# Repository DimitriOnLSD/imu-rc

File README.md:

# IMU-RC
This repository contains the final project for an Electronics and Computer Engineering degree: IMU-RC, an innovative hand-held controller for RC cars.

## Features
### Hand Unit
The hand unit is a battery-powered controller featuring:

- ESP32-S3 WROOM module on a custom PCB designed in KiCad.
- LSM6DSO IMU sensor for motion detection.
- BLE communication using a client/server protocol with the RC car.
- OLED screen (128x32) for menu options, diagnostics, and sensitivity adjustments.
- Four buttons for navigation: Back, Up, Select, Down.
- RGB LED to display battery or communication status.
- Battery Management System (BMS) with BQ297 and MCP73831 to charge a 3.7V 250mAh LiPo battery via USB-C.
- BOOT and RESET buttons for easy firmware handling.

### Gesture-Based Control
Control the RC car with intuitive hand gestures:

- Lean forward: Car moves forward.
- Lean backward: Car reverses.
- Lean left or right: Car rotates left or right.
- Control mode toggle: For 4-motor vehicles with omni-directional wheels, enable sideways movement for strafing.

### Additional Features
- Car stats menu: Check car battery levels.
- Safety mechanism: Infrared proximity sensors prevent collision with walls/objects:
  - 2-motor cars: Front and back sensors.
  - 4-motor cars: Side sensors added for additional safety during strafing.
  
### Technical Highlights
- Custom PCB: Designed in KiCad for compact, efficient performance.
- Battery Management: MCP73831 handles charging, and BQ297 ensures protection against overcharging/discharging.
- Versatile Control: Adaptable to different RC car configurations (2-motor or 4-motor).
- OLED Menu System: Offers detailed settings, diagnostics, and real-time feedback.

### Usage
IMU-RC is designed to bring modern, intuitive control to RC vehicles, making it a perfect blend of technology and engineering creativity.

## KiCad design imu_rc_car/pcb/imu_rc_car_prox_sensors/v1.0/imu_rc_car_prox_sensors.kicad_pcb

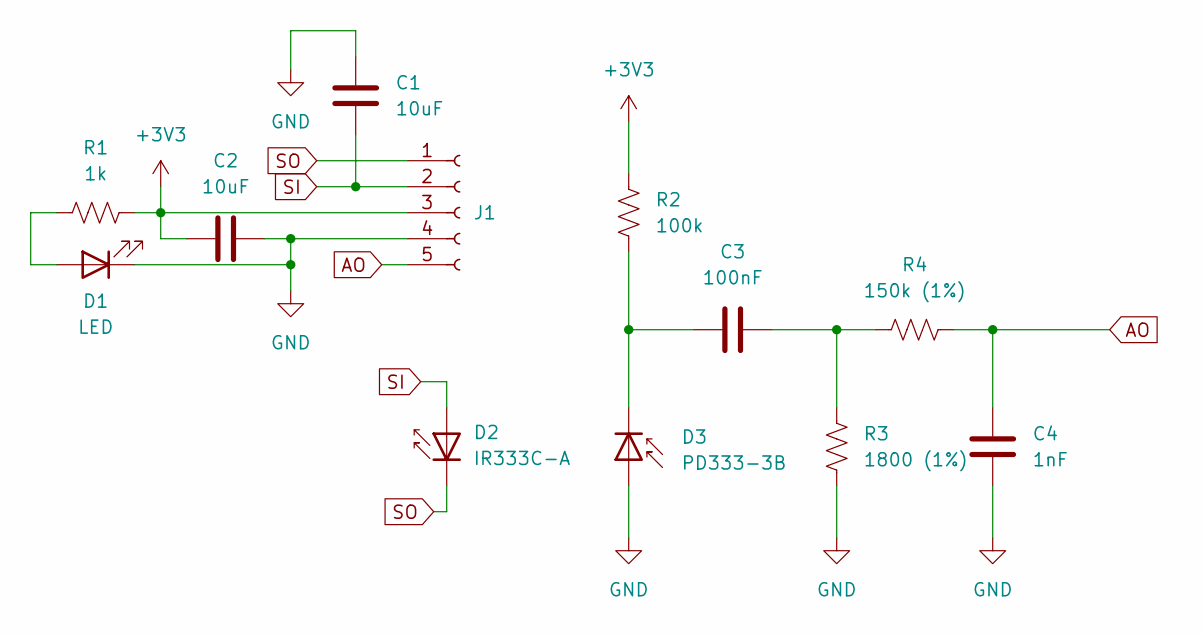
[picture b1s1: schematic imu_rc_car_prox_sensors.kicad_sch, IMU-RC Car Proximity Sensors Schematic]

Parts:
C1, C2: 10uF; C_0805_2012Metric
C3: 100nF; C_0805_2012Metric
C4: 1nF; C_0805_2012Metric
D1: LED; LED_0805_2012Metric
D2: IR333C-A; LED_D5.0mm_Horizontal_O1.27mm_Z3.0mm_Clear
D3: PD333-3B; LED_D5.0mm_Horizontal_O1.27mm_Z3.0mm_IRBlack
J1: Conn_01x05_Socket; JST_PH_S5B-PH-SM4-TB_1x05-1MP_P2.00mm_Horizontal
R1: 1k; R_0805_2012Metric
R2: 100k; R_0805_2012Metric
R3: 1800 (1%); R_0805_2012Metric
R4: 150k (1%); R_0805_2012Metric

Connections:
+3V3: C2.2, J1.3, R1.2, R2.2
AO: C4.2, J1.5, R4.1
GND: C1.1, C2.1, C4.1, D1.1 (K), D3.2 (A), J1.4, R3.1
unnamed: C3.2, R3.2, R4.2
unnamed: D1.2 (A), R1.1
unnamed: C3.1, D3.1 (K), R2.1
SI: C1.2, D2.2 (A), J1.2
SO: D2.1 (K), J1.1

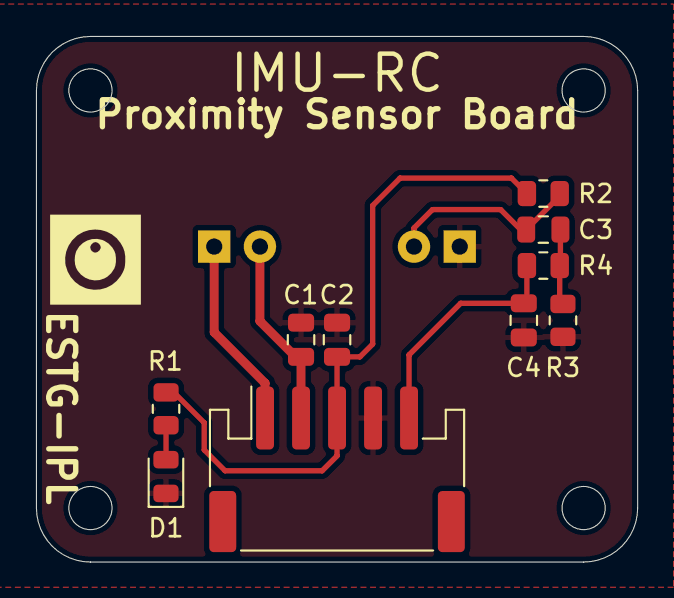
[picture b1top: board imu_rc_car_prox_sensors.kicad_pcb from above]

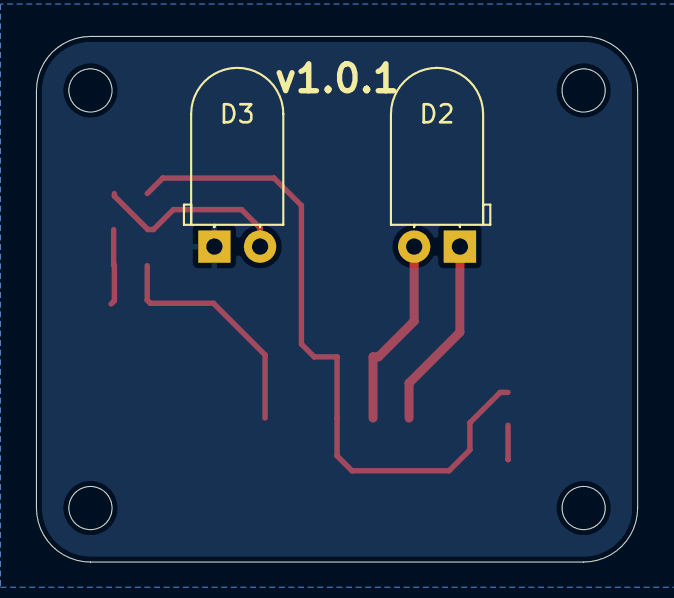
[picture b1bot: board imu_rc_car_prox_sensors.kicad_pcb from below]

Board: 2 copper layers, 33.4 x 29.2 mm, 12 parts (2 on the bottom side), 8 nets.

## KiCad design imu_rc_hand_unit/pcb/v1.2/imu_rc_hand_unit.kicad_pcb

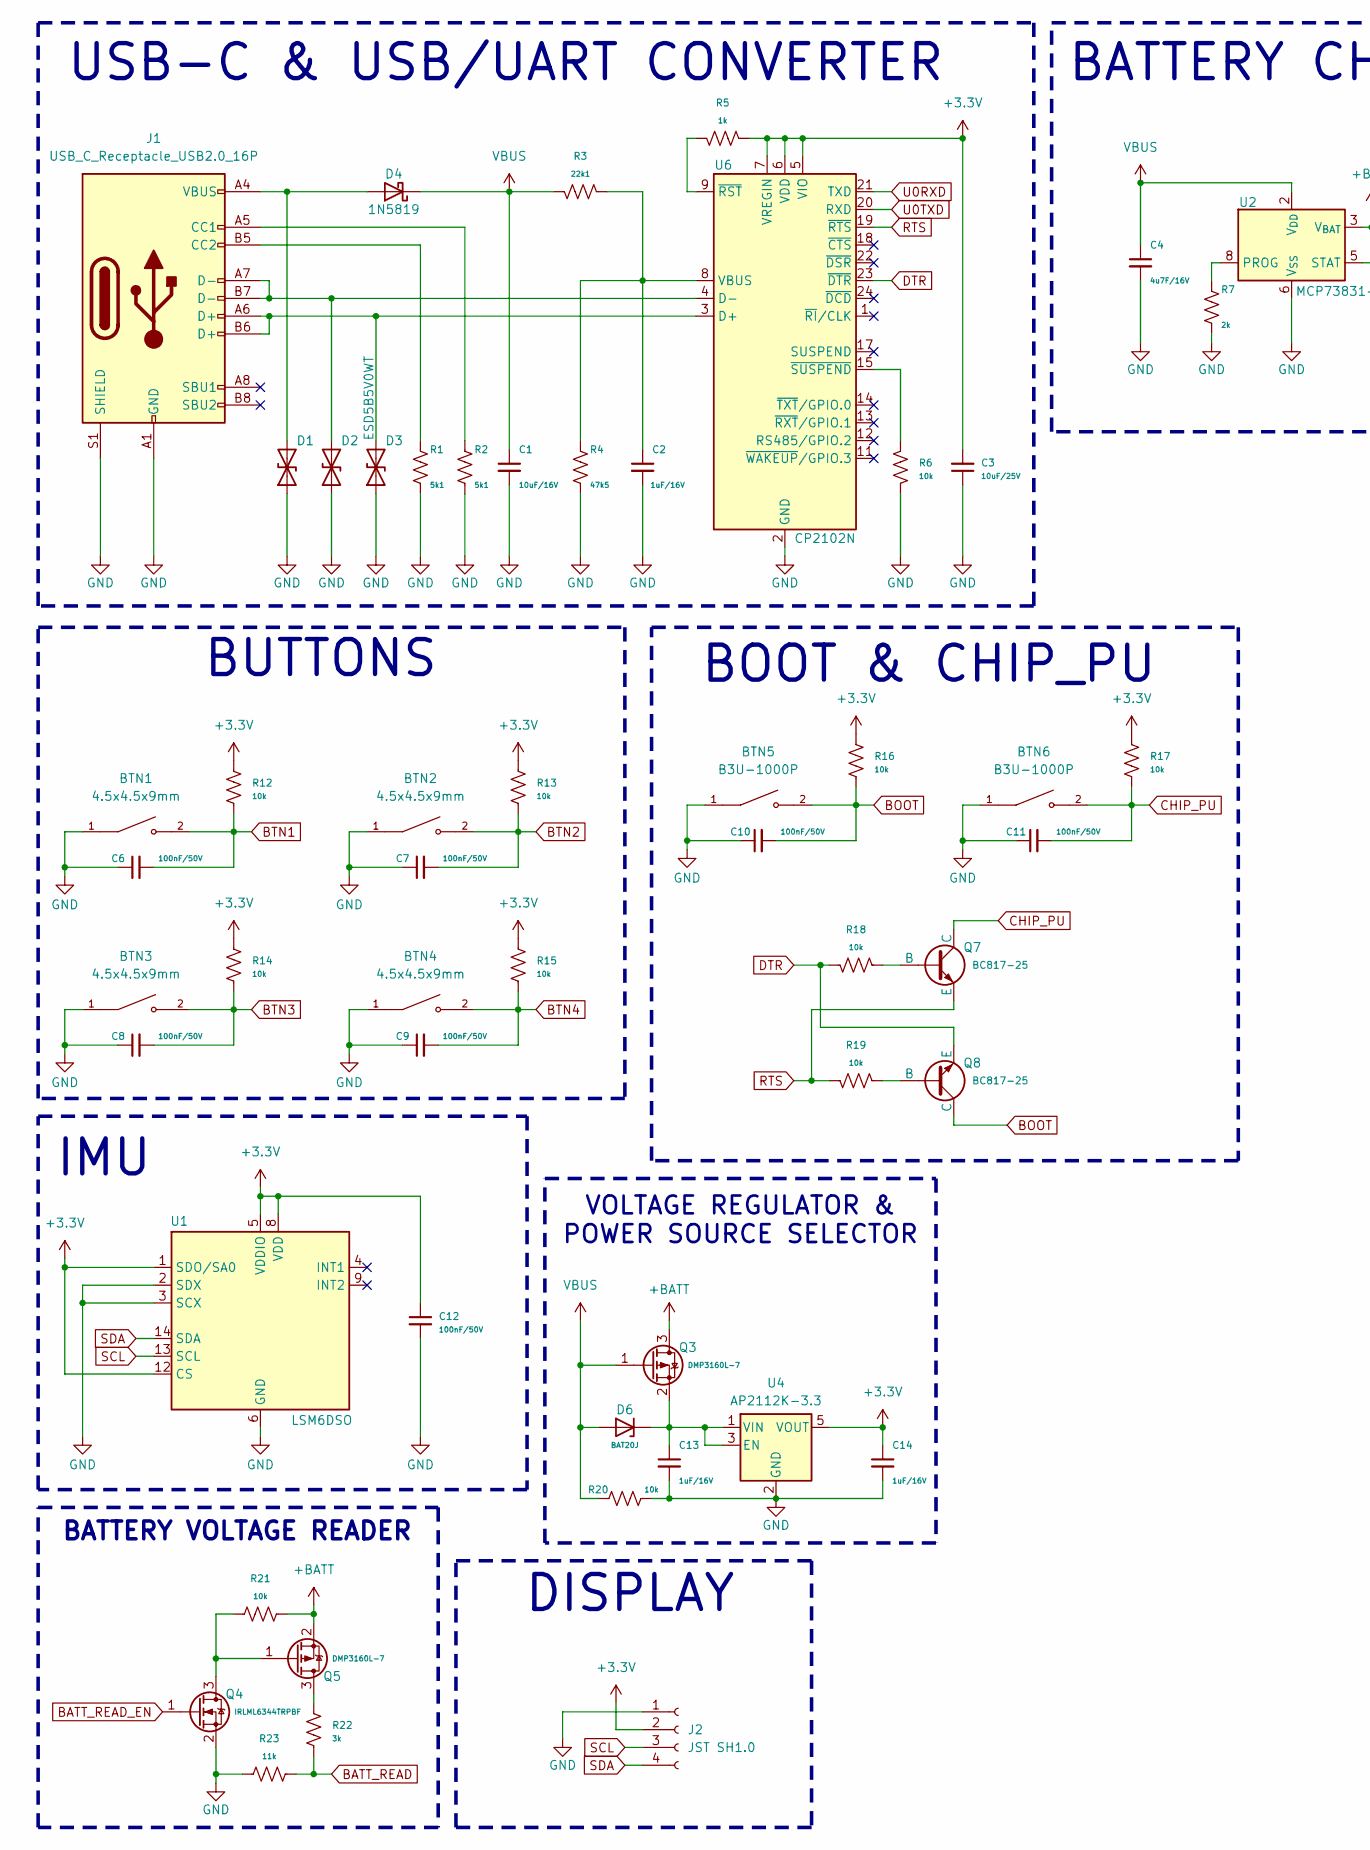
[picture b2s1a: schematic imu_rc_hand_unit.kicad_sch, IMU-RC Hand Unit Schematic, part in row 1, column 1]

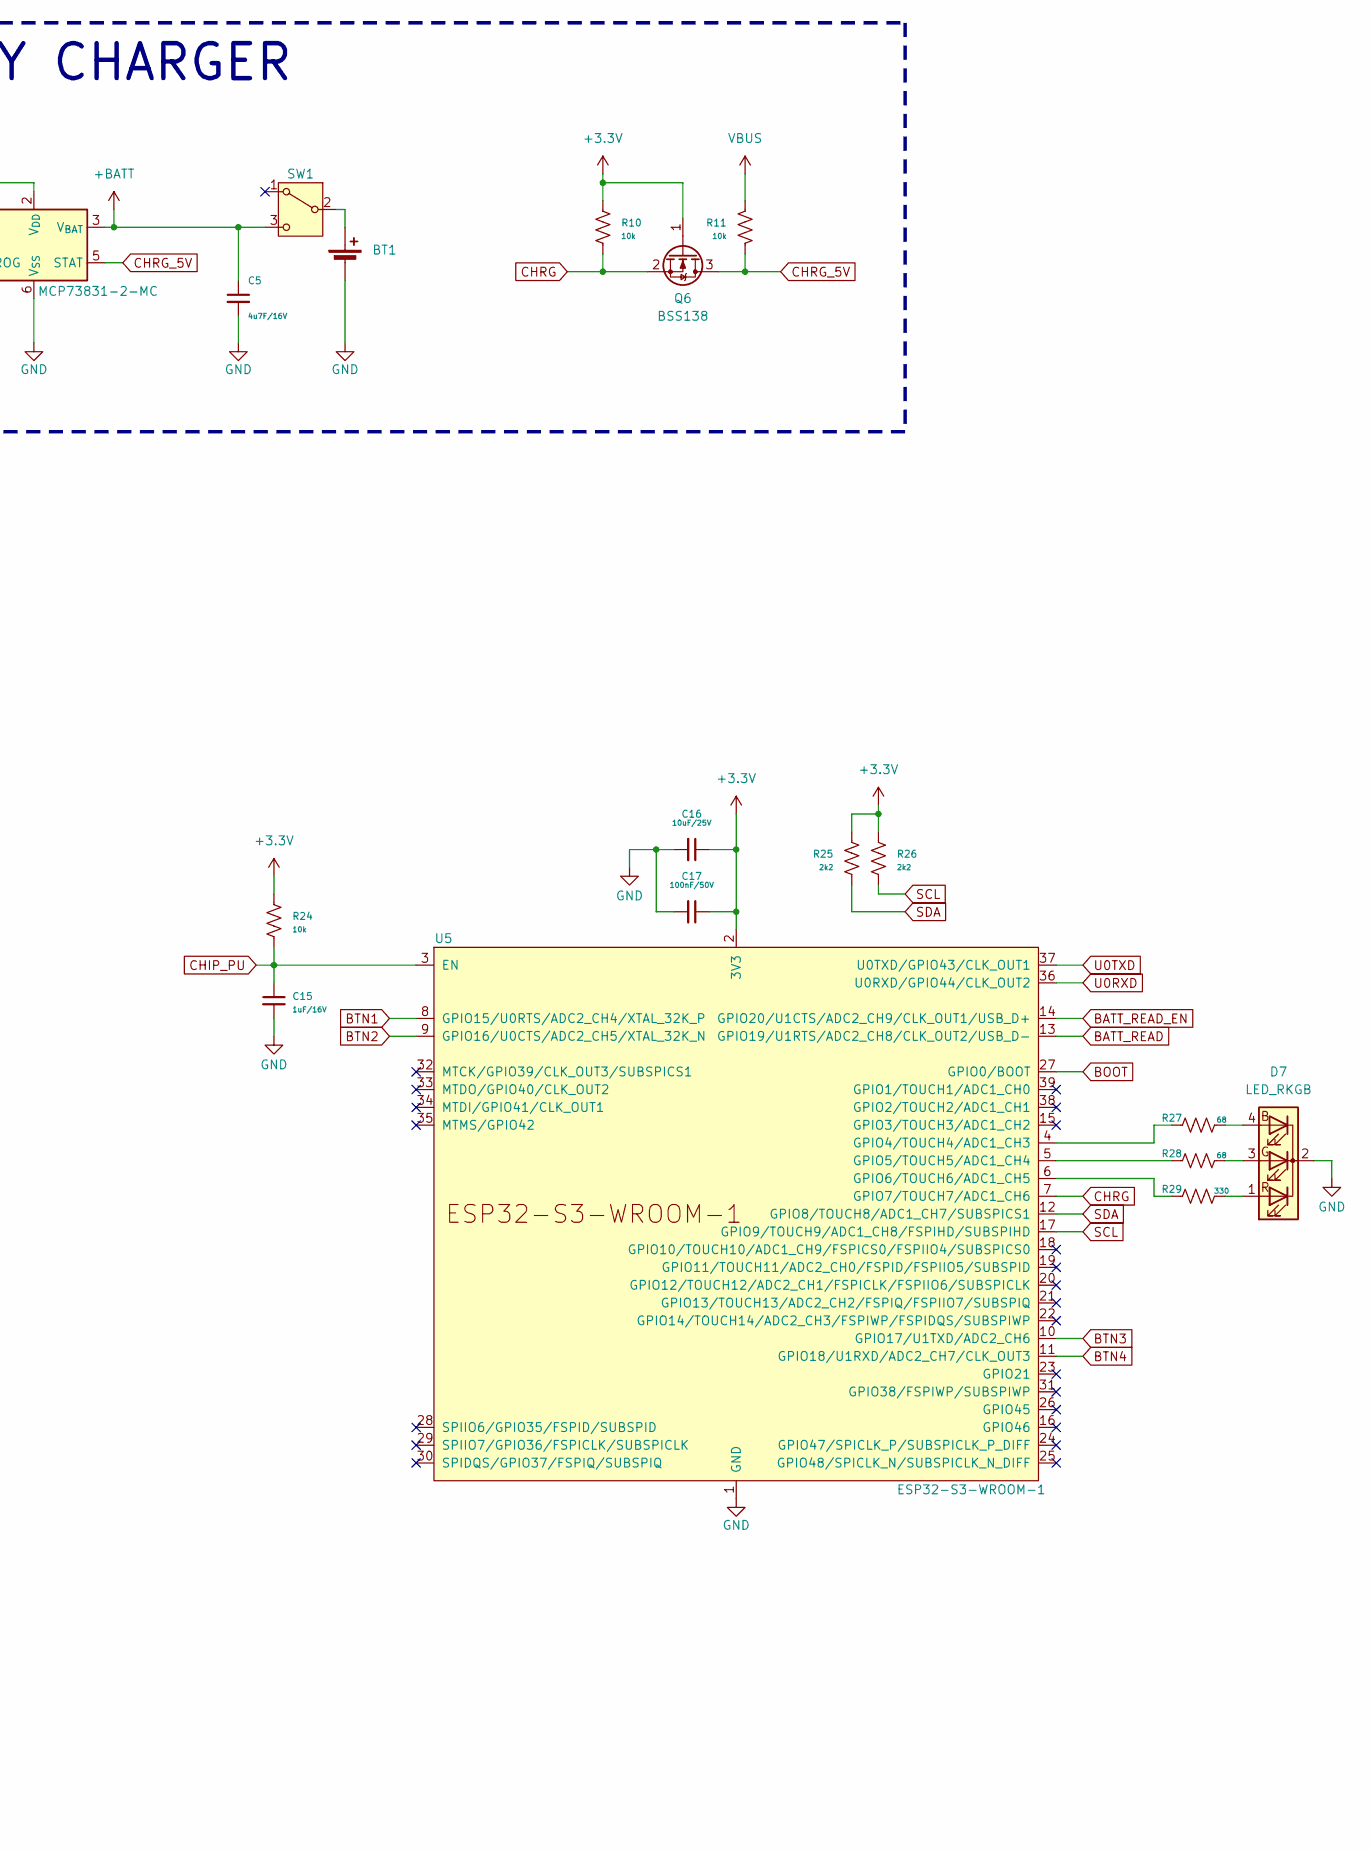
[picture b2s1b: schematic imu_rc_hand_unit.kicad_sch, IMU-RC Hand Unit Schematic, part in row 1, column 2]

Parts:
BT1: LiPo 3.7V 600mAh; JST_PH_S2B-PH-K_1x02_P2.00mm_Horizontal
BTN1, BTN2, BTN3, BTN4: 4.5x4.5x9mm; SW_SPST_PTS647_Sx50
BTN5, BTN6: B3U-1000P; SW_SPST_B3U-1000P
C1: 10uF/16V; C_0805_2012Metric
C2: 1uF/16V; C_0603_1608Metric
C3: 10uF/25V; C_0603_1608Metric
C4, C5: 4u7F/16V; C_0603_1608Metric
C6, C7, C8, C9, C10, C11, C12, C17: 100nF/50V; C_0805_2012Metric
C13, C14, C15: 1uF/16V; C_0805_2012Metric
C16: 10uF/25V; C_0805_2012Metric
D1, D2, D3: ESD5B5V0WT; D_SOD-523
D4: 1N5819; D_SOD-123
D6: BAT20J; D_SOD-323
D7: LED_RKGB; LED_D5.0mm-4_RKGB
J1: USB_C_Receptacle_USB2.0_16P; USB_C_Receptacle_GCT_USB4105-xx-A_16P_TopMnt_Horizontal
J2: JST SH1.0; JST_SH_SM04B-SRSS-TB_1x04-1MP_P1.00mm_Horizontal
Q3, Q5: DMP3160L-7; SOT-23
Q4: IRLML6344TRPBF; SOT-23
Q6: BSS138; SOT-23
Q7, Q8: BC817-25; SOT-23
R1, R2: 5k1; R_0805_2012Metric
R3: 22k1; R_0805_2012Metric
R4: 47k5; R_0805_2012Metric
R5: 1k; R_0805_2012Metric
R6, R10, R11, R12, R13, R14, R15, R16, R17, R18, R19, R20, R21, R24: 10k; R_0805_2012Metric
R7: 2k; R_0805_2012Metric
R22: 3k; R_0805_2012Metric
R23: 11k; R_0805_2012Metric
R25, R26: 2k2; R_0805_2012Metric
R27, R28: 68; R_0805_2012Metric
R29: 330; R_0805_2012Metric
SW1: SW_SPDT; SW_Slide_SPDT_Angled_CK_OS102011MA1Q
U1: LSM6DSO; LGA-14L_3x2.5mm_P0.5mm
U2: MCP73831-2-MC; DFN-8-1EP_3x2mm_P0.5mm_EP1.7x1.4mm
U4: AP2112K-3.3; SOT-23-5
U5: ESP32-S3-WROOM-1
U6: CP2102N; QFN-24-1EP_4x4mm_P0.5mm_EP2.6x2.6mm

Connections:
+3.3V: C3.2, C12.1, C14.1, C16.1, C17.1, J2.2, Q6.1 (G), R5.2, R10.2, R12.2, R13.2, R14.2, R15.2, R16.2, R17.2, R24.2, R25.1, R26.2, U1.1 (SDO/SA0), U1.5 (VDDIO), U1.8 (VDD), U1.12 (CS), U4.5 (VOUT), U5.2 (3V3), U6.5 (VIO), U6.6 (VDD), U6.7 (VREGIN)
BATT_READ: R22.2, R23.1, U5.13 (GPIO19/U1RTS/ADC2_CH8/CLK_OUT2/USB_D-)
BATT_READ_EN: Q4.1 (G), U5.14 (GPIO20/U1CTS/ADC2_CH9/CLK_OUT1/USB_D+)
BOOT: BTN5.2, C10.2, Q8.1 (C), R16.1, U5.27 (GPIO0/BOOT); also elsewhere on the board
BTN1: BTN1.2, C6.2, R12.1, U5.8 (GPIO15/U0RTS/ADC2_CH4/XTAL_32K_P)
BTN2: BTN2.2, C7.2, R13.1, U5.9 (GPIO16/U0CTS/ADC2_CH5/XTAL_32K_N)
BTN3: BTN3.2, C8.2, R14.1, U5.10 (GPIO17/U1TXD/ADC2_CH6)
BTN4: BTN4.2, C9.2, R15.1, U5.11 (GPIO18/U1RXD/ADC2_CH7/CLK_OUT3)
CHIP_PU: BTN6.2, C11.2, C15.1, Q7.1 (C), R17.1, R24.1, U5.3 (EN); also elsewhere on the board
CHRG: Q6.2 (S), R10.1, U5.7 (GPIO7/TOUCH7/ADC1_CH6)
CHRG_5V: Q6.3 (D), R11.1, U2.5 (STAT)
DTR: Q8.3 (E), R18.1, U6.23 (~DTR)
unnamed: BT1.1 (+), SW1.2 (B)
unnamed: D1.2 (A2), D4.2 (A), J1.A4 (VBUS), J1.A9 (VBUS), J1.B4 (VBUS), J1.B9 (VBUS)
unnamed: D2.2 (A2), J1.A7 (D-), J1.B7 (D-), U6.4 (D-)
unnamed: D3.2 (A2), J1.A6 (D+), J1.B6 (D+), U6.3 (D+)
unnamed: C13.1, D6.1 (K), Q3.2 (S), U4.1 (VIN), U4.3 (EN)
unnamed: D7.4 (BA), R27.1
unnamed: D7.3 (GA), R28.1
unnamed: D7.1 (RA), R29.1
unnamed: J1.A5 (CC1), R2.2
unnamed: J1.B5 (CC2), R1.2
unnamed: Q4.3 (D), Q5.1 (G), R21.1
unnamed: Q5.3 (D), R22.1
unnamed: Q7.2 (B), R18.2
unnamed: Q8.2 (B), R19.2
unnamed: R7.1, U2.8 (PROG)
unnamed: R27.2, U5.4 (GPIO4/TOUCH4/ADC1_CH3)
unnamed: R28.2, U5.5 (GPIO5/TOUCH5/ADC1_CH4)
unnamed: R29.2, U5.6 (GPIO6/TOUCH6/ADC1_CH5)
unnamed: C2.1, R3.1, R4.2, U6.8 (VBUS)
unnamed: R5.1, U6.9 (~RST)
unnamed: R6.1, U6.15 (~SUSPEND)
RTS: Q7.3 (E), R19.1, U6.19 (~RTS)
SCL: J2.3, R26.1, U1.13 (SCL), U5.17 (GPIO9/TOUCH9/ADC1_CH8/FSPIHD/SUBSPIHD)
SDA: J2.4, R25.2, U1.14 (SDA), U5.12 (GPIO8/TOUCH8/ADC1_CH7/SUBSPICS1)
U0RXD: U5.36 (U0RXD/GPIO44/CLK_OUT2), U6.21 (TXD)
U0TXD: U5.37 (U0TXD/GPIO43/CLK_OUT1), U6.20 (RXD)
VBUS: C1.1, C4.1, D4.1 (K), D6.2 (A), Q3.1 (G), R3.2, R11.2, R20.2, U2.1 (V_{DD}), U2.2 (V_{DD})

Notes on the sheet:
VOLTAGE REGULATOR & POWER SOURCE SELECTOR
BATTERY CHARGER
BUTTONS
BOOT & CHIP_PU
USB-C & USB/UART CONVERTER
BATTERY VOLTAGE READER
IMU
DISPLAY

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
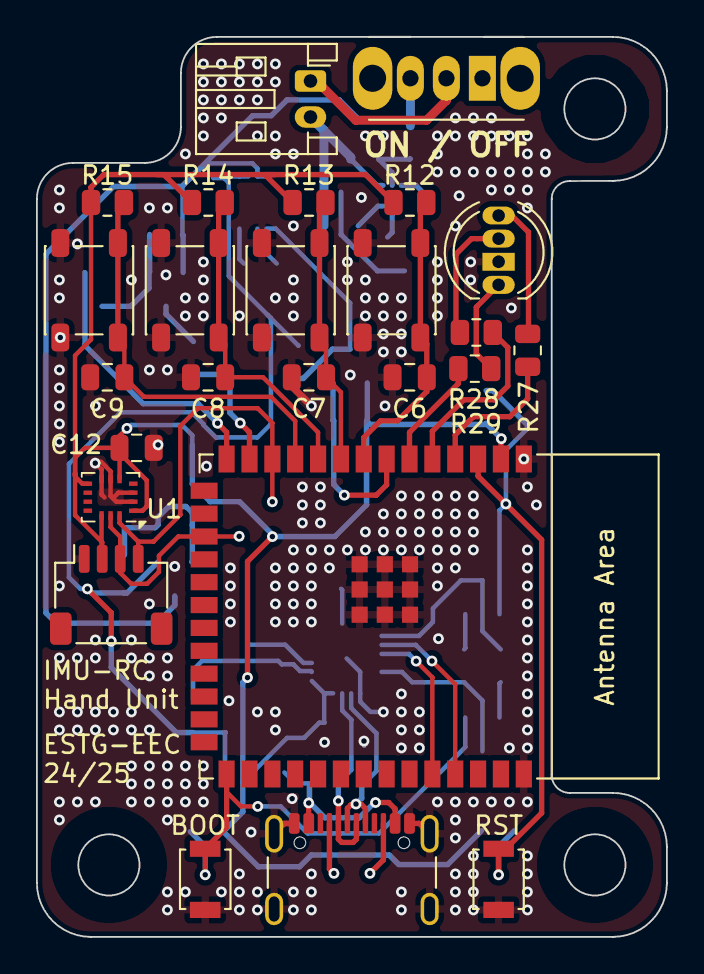
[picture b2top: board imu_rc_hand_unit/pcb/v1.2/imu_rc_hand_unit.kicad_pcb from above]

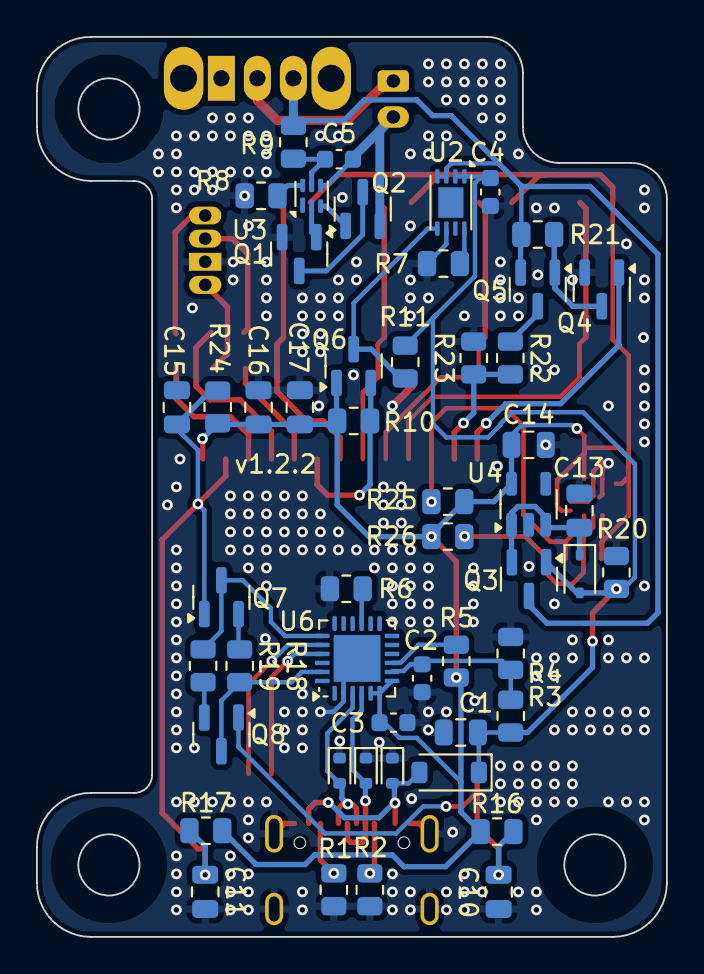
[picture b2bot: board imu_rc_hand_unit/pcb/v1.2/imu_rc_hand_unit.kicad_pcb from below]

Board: 2 copper layers, 35.0 x 50.0 mm, 76 parts (51 on the bottom side), 47 nets.

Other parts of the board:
BOOT: B3U-1000P; SW_SPST_B3U-1000P
Q1, Q2: IRLML6344TRPBF; SOT-23
R8: 2k2; R_0805_2012Metric
R9: 330; R_0805_2012Metric
RST: B3U-1000P; SW_SPST_B3U-1000P
U3: BQ297xy; WSON-6_1.5x1.5mm_P0.5mm

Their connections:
BOOT: BOOT.2; also elsewhere on the board
CHIP_PU: RST.2; also elsewhere on the board
unnamed: Q1.3 (D), Q2.3 (D)
unnamed: Q1.1 (G), U3.2 (Cout)
unnamed: Q2.1 (G), U3.3 (Dout)
unnamed: R8.2, U3.6 (V-)

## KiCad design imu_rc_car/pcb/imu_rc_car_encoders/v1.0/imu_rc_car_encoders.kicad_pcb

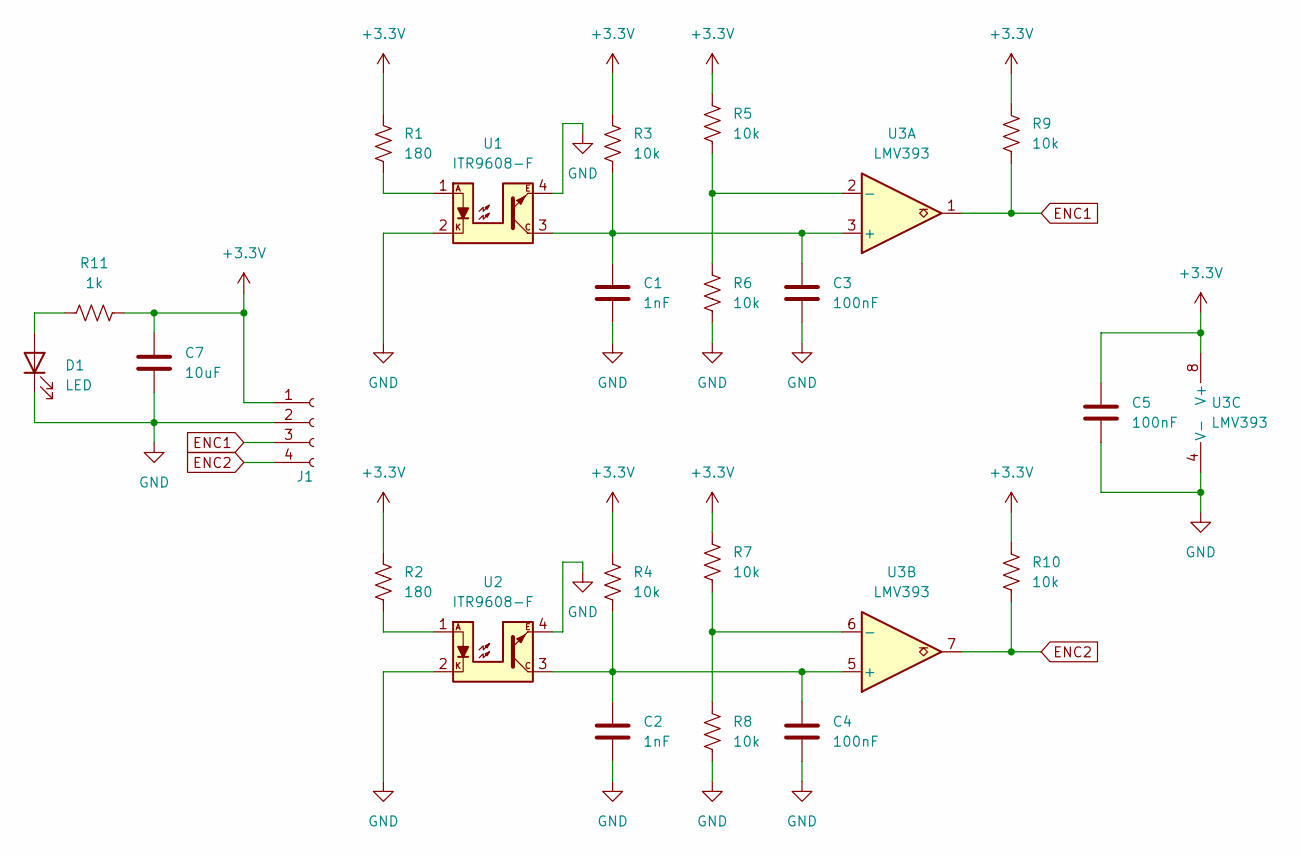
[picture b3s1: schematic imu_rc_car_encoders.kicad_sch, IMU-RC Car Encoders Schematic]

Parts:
C1, C2: 1nF; C_0805_2012Metric
C3, C4, C5: 100nF; C_0805_2012Metric
C7: 10uF; C_0805_2012Metric
D1: LED; LED_0805_2012Metric
J1: Conn_01x04_Socket; JST_PH_S4B-PH-SM4-TB_1x04-1MP_P2.00mm_Horizontal
R1, R2: 180; R_0805_2012Metric
R3, R4, R5, R6, R7, R8, R9, R10: 10k; R_0805_2012Metric
R11: 1k; R_0805_2012Metric
U1, U2: ITR9608-F; Everlight_ITR9608-F
U3: LMV393; SOIC-8_3.9x4.9mm_P1.27mm

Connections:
+3.3V: C5.1, C7.1, J1.1, R1.1, R2.1, R3.1, R4.1, R5.1, R7.1, R9.1, R10.1, R11.2, U3.8 (V+)
ENC1: J1.3, R9.2, U3.1
ENC2: J1.4, R10.2, U3.7
GND: C1.2, C2.2, C3.2, C4.2, C5.2, C7.2, D1.1 (K), J1.2, R6.2, R8.2, U1.2, U1.4, U2.2, U2.4, U3.4 (V-)
unnamed: D1.2 (A), R11.1
unnamed: R1.2, U1.1
unnamed: R2.2, U2.1
unnamed: C1.1, C3.1, R3.2, U1.3, U3.3 (+)
unnamed: R5.2, R6.1, U3.2 (-)
unnamed: C2.1, C4.1, R4.2, U2.3, U3.5 (+)
unnamed: R7.2, R8.1, U3.6 (-)

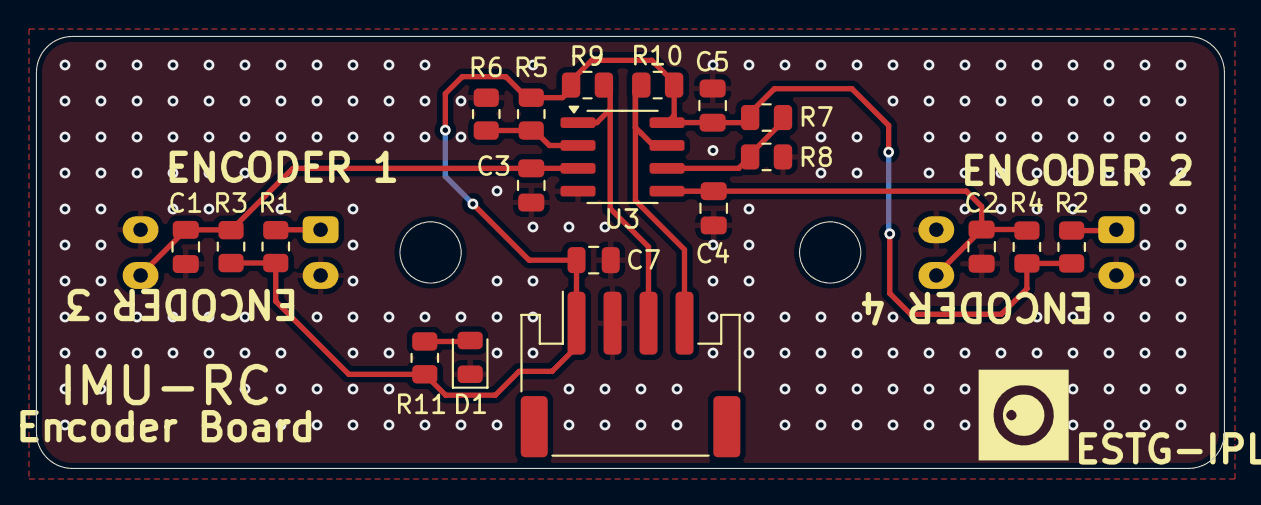
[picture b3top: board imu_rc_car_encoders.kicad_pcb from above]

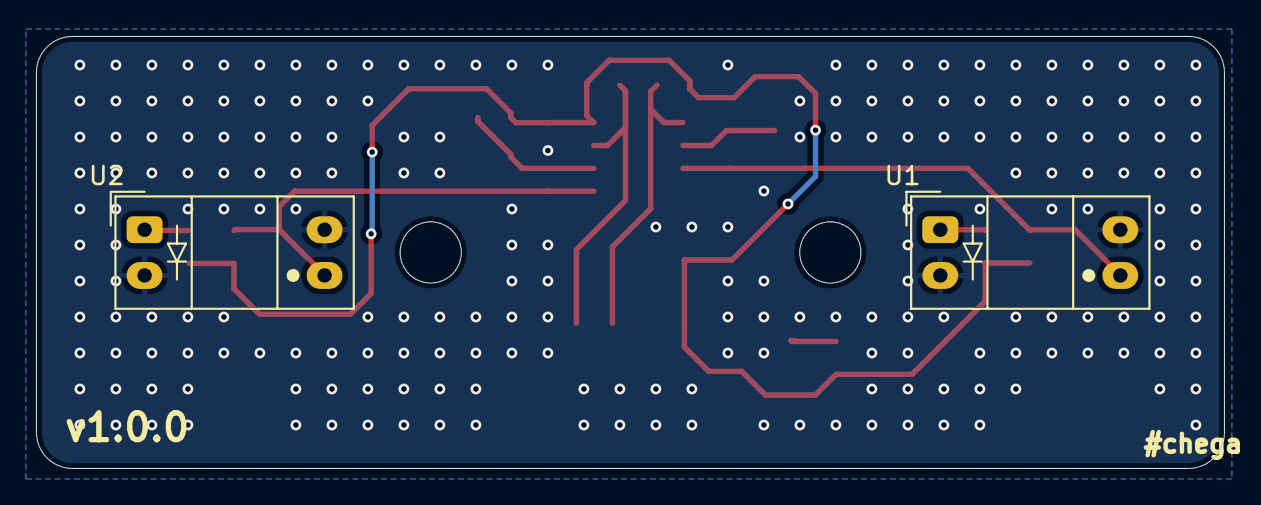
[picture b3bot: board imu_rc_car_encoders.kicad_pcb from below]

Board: 2 copper layers, 66.0 x 24.0 mm, 22 parts (2 on the bottom side), 11 nets.

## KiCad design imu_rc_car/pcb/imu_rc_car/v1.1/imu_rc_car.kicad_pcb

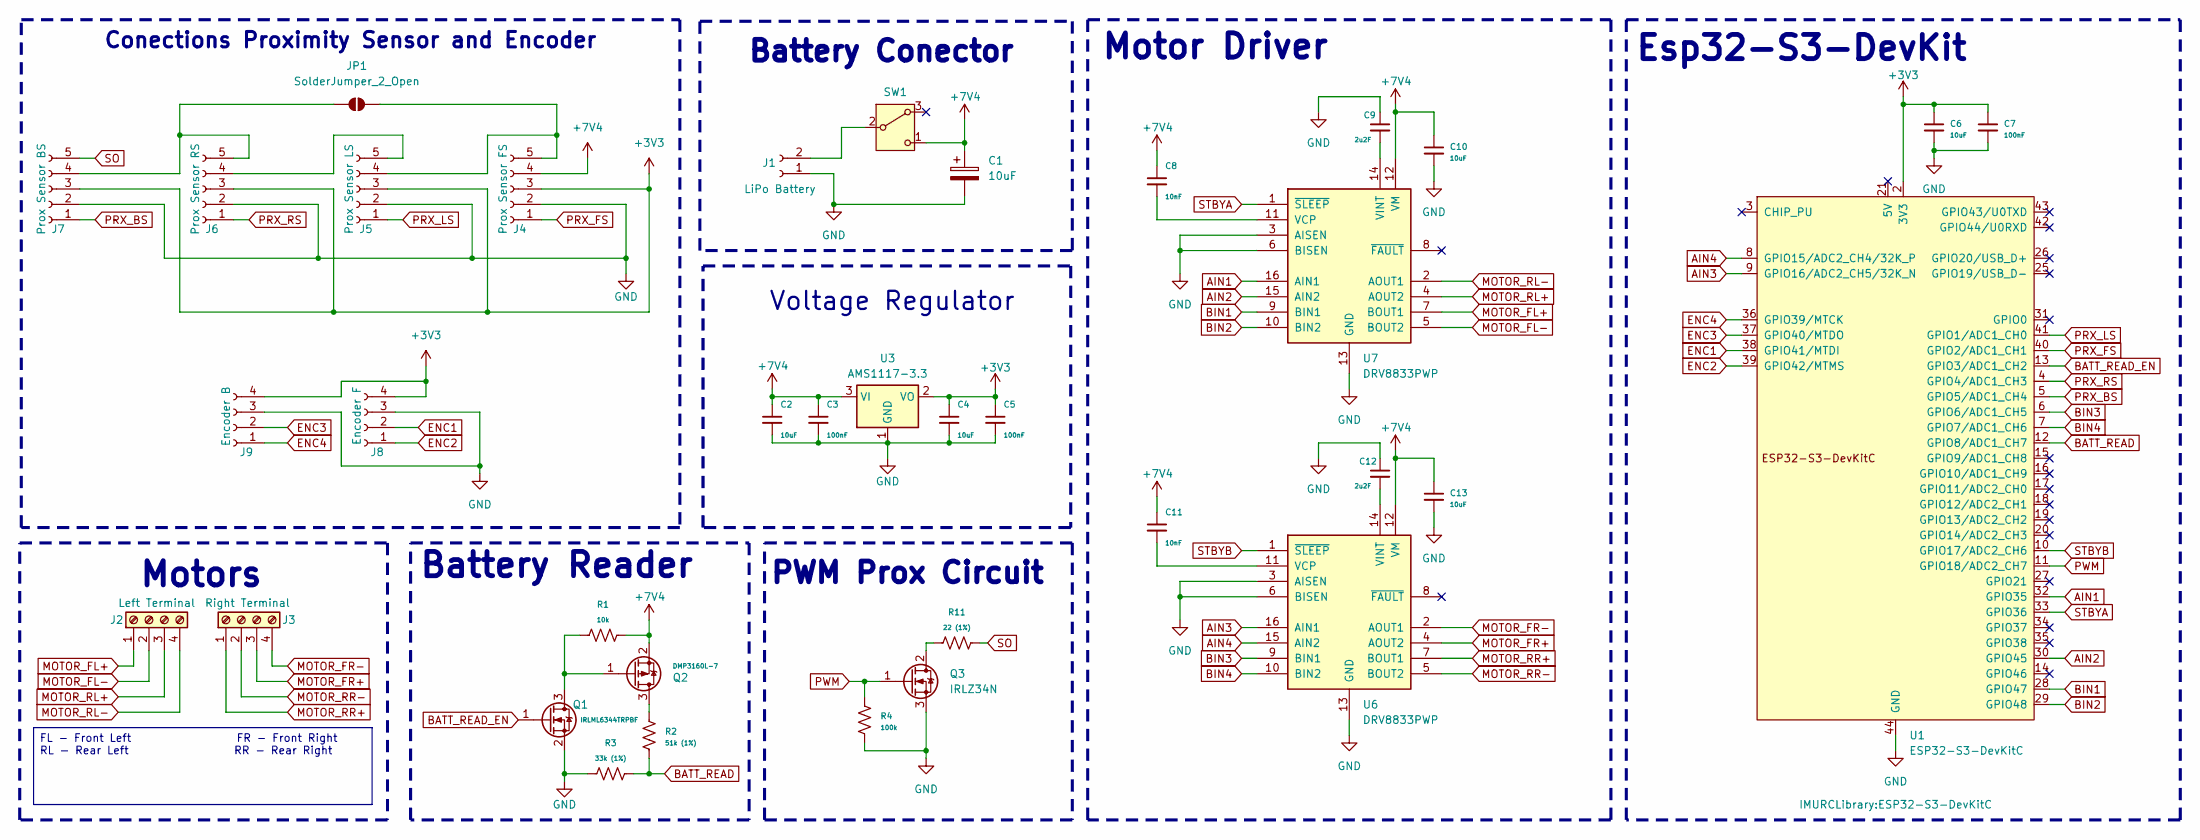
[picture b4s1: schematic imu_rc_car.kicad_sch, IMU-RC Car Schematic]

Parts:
C1: 10uF; CP_Elec_5x5.7
C2, C4, C6, C10, C13: 10uF; C_0805_2012Metric
C3, C5, C7: 100nF; C_0805_2012Metric
C8, C11: 10nF; C_0805_2012Metric
C9, C12: 2u2F; C_0805_2012Metric
J1: LiPo Battery; TerminalBlock_MaiXu_MX126-5.0-02P_1x02_P5.00mm
J2: Left Terminal; TerminalBlock_Xinya_XY308-2.54-4P_1x04_P2.54mm_Horizontal
J3: Right Terminal; TerminalBlock_Xinya_XY308-2.54-4P_1x04_P2.54mm_Horizontal
J4: Prox Sensor FS; JST_PH_S5B-PH-SM4-TB_1x05-1MP_P2.00mm_Horizontal
J5: Prox Sensor LS; JST_PH_S5B-PH-SM4-TB_1x05-1MP_P2.00mm_Horizontal
J6: Prox Sensor RS; JST_PH_S5B-PH-SM4-TB_1x05-1MP_P2.00mm_Horizontal
J7: Prox Sensor BS; JST_PH_S5B-PH-SM4-TB_1x05-1MP_P2.00mm_Horizontal
J8: Encoder F; JST_PH_S4B-PH-SM4-TB_1x04-1MP_P2.00mm_Horizontal
J9: Encoder B; JST_PH_S4B-PH-SM4-TB_1x04-1MP_P2.00mm_Horizontal
JP1: SolderJumper_2_Open; SolderJumper-2_P1.3mm_Open_RoundedPad1.0x1.5mm
Q1: IRLML6344TRPBF; SOT-23
Q2: DMP3160L-7; SOT-23
Q3: IRLZ34N; TO-263-3_TabPin2
R1: 10k; R_0805_2012Metric
R2: 51k (1%); R_0805_2012Metric
R3: 33k (1%); R_0805_2012Metric
R4: 100k; R_0805_2012Metric
R11: 22 (1%); R_0805_2012Metric
SW1: SW_Nidec_CAS-120A1; SW_Slide_SPDT_Angled_CK_OS102011MA1Q
U1: ESP32-S3-DevKitC
U3: AMS1117-3.3; SOT-223-3_TabPin2
U6, U7: DRV8833PWP; HTSSOP-16-1EP_4.4x5mm_P0.65mm_EP3.4x5mm_Mask2.46x2.31mm_The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

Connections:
+3V3: C4.1, C5.1, C6.1, C7.1, J4.3, J5.3, J6.3, J7.3, J8.4, J9.4, U1.1 (3V3), U1.2 (3V3), U3.2 (VO)
+7V4: C1.1, C2.1, C3.1, C8.1, C10.1, C11.1, C13.1, J4.4, Q2.2 (S), R1.2, SW1.1 (C), U3.3 (VI), U6.12 (VM), U7.12 (VM)
AIN1: U1.32 (GPIO35), U7.16 (AIN1)
AIN2: U1.30 (GPIO45), U7.15 (AIN2)
AIN3: U1.9 (GPIO16/ADC2_CH5/32K_N), U6.16 (AIN1)
AIN4: U1.8 (GPIO15/ADC2_CH4/32K_P), U6.15 (AIN2)
BATT_READ: R2.2, R3.1, U1.12 (GPIO8/ADC1_CH7)
BATT_READ_EN: Q1.1 (G), U1.13 (GPIO3/ADC1_CH2)
BIN1: U1.28 (GPIO47), U7.9 (BIN1)
BIN2: U1.29 (GPIO48), U7.10 (BIN2)
BIN3: U1.6 (GPIO6/ADC1_CH5), U6.9 (BIN1)
BIN4: U1.7 (GPIO7/ADC1_CH6), U6.10 (BIN2)
ENC1: J8.2, U1.38 (GPIO41/MTDI)
ENC2: J8.1, U1.39 (GPIO42/MTMS)
ENC3: J9.2, U1.37 (GPIO40/MTDO)
ENC4: J9.1, U1.36 (GPIO39/MTCK)
GND: C1.2, C2.2, C3.2, C4.2, C5.2, C6.2, C7.2, C9.1, C10.2, C12.1, C13.2, J1.1, J4.2, J5.2, J6.2, J7.2, J8.3, J9.3, Q1.2 (S), Q3.3 (S), R3.2, R4.2, U1.22 (GND), U1.23 (GND), U1.24 (GND), U1.44 (GND), U3.1 (GND), U6.3 (AISEN), U6.6 (BISEN), U6.13 (GND), U6.17 (GND), U7.3 (AISEN), U7.6 (BISEN), U7.13 (GND), U7.17 (GND)
MOTOR_FL+: J2.1, U7.7 (BOUT1)
MOTOR_FL-: J2.2, U7.5 (BOUT2)
MOTOR_FR+: J3.3, U6.4 (AOUT2)
MOTOR_FR-: J3.4, U6.2 (AOUT1)
MOTOR_RL+: J2.3, U7.4 (AOUT2)
MOTOR_RL-: J2.4, U7.2 (AOUT1)
MOTOR_RR+: J3.1, U6.7 (BOUT1)
MOTOR_RR-: J3.2, U6.5 (BOUT2)
unnamed: J1.2, SW1.2 (B)
unnamed: J4.5, J5.4, JP1.2 (B)
unnamed: J5.5, J6.4
unnamed: J6.5, J7.4, JP1.1 (A)
unnamed: Q1.3 (D), Q2.1 (G), R1.1
unnamed: Q2.3 (D), R2.1
unnamed: Q3.2 (D), R11.1
unnamed: C11.2, U6.11 (VCP)
unnamed: C12.2, U6.14 (VINT)
unnamed: C8.2, U7.11 (VCP)
unnamed: C9.2, U7.14 (VINT)
PRX_BS: J7.1, U1.5 (GPIO5/ADC1_CH4)
PRX_FS: J4.1, U1.40 (GPIO2/ADC1_CH1)
PRX_LS: J5.1, U1.41 (GPIO1/ADC1_CH0)
PRX_RS: J6.1, U1.4 (GPIO4/ADC1_CH3)
PWM: Q3.1 (G), R4.1, U1.11 (GPIO18/ADC2_CH7)
SO: J7.5, R11.2
STBYA: U1.33 (GPIO36), U7.1 (~SLEEP)
STBYB: U1.10 (GPIO17/ADC2_CH6), U6.1 (~SLEEP)

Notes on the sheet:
Voltage Regulator
Battery Conector
PWM Prox Circuit
Motor Driver
Conections Proximity Sensor and Encoder
Esp32-S3-DevKit
Motors
Battery Reader
FL - Front Left FR - Front Right RL - Rear Left RR - Rear Right

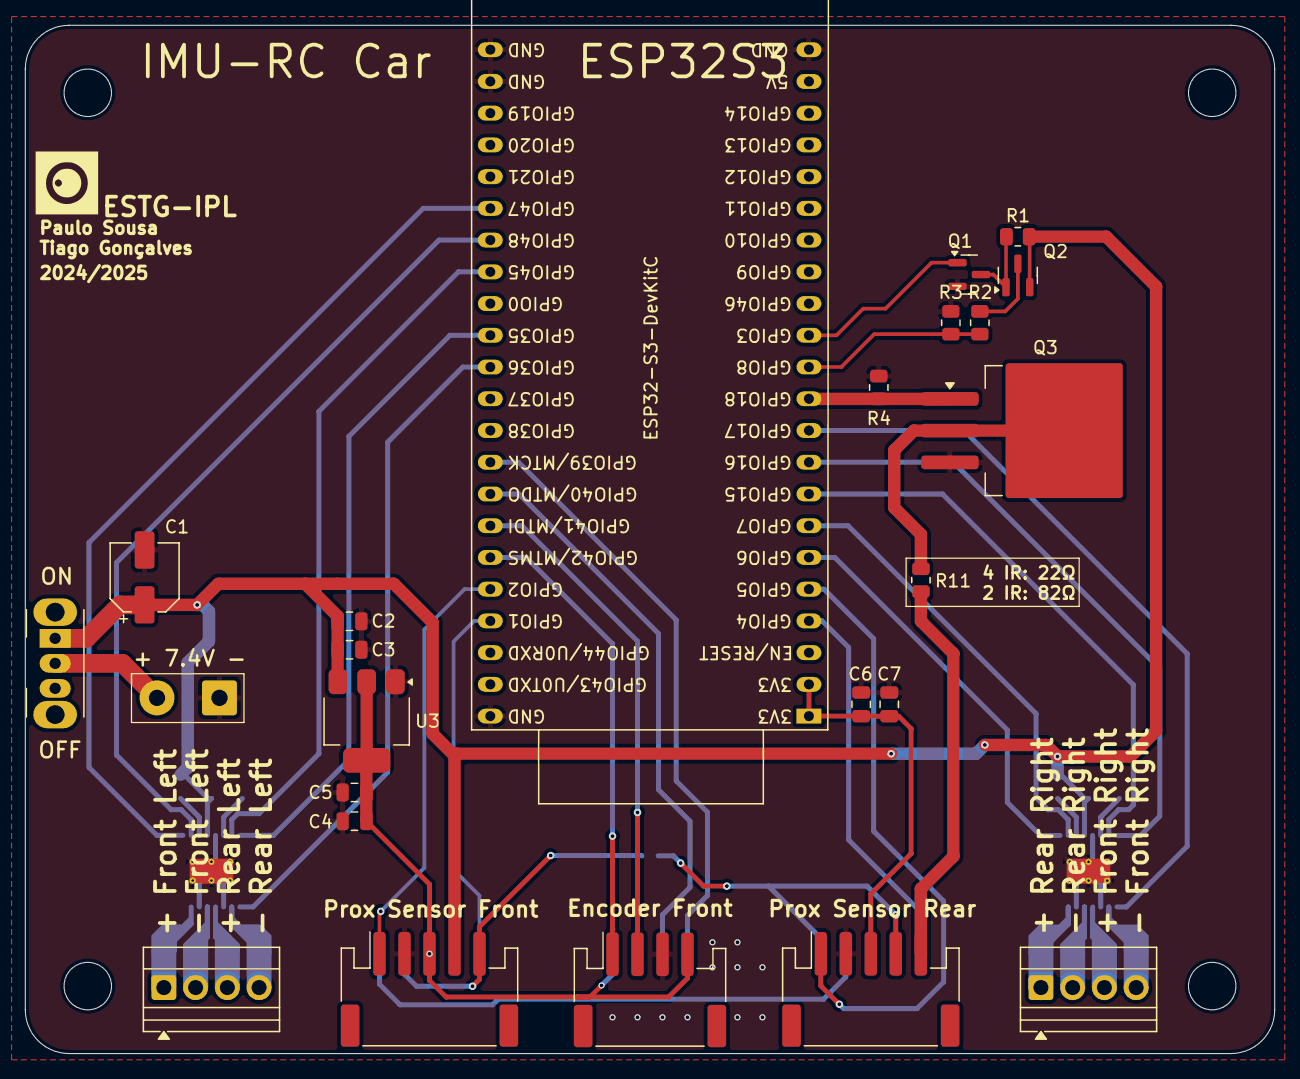
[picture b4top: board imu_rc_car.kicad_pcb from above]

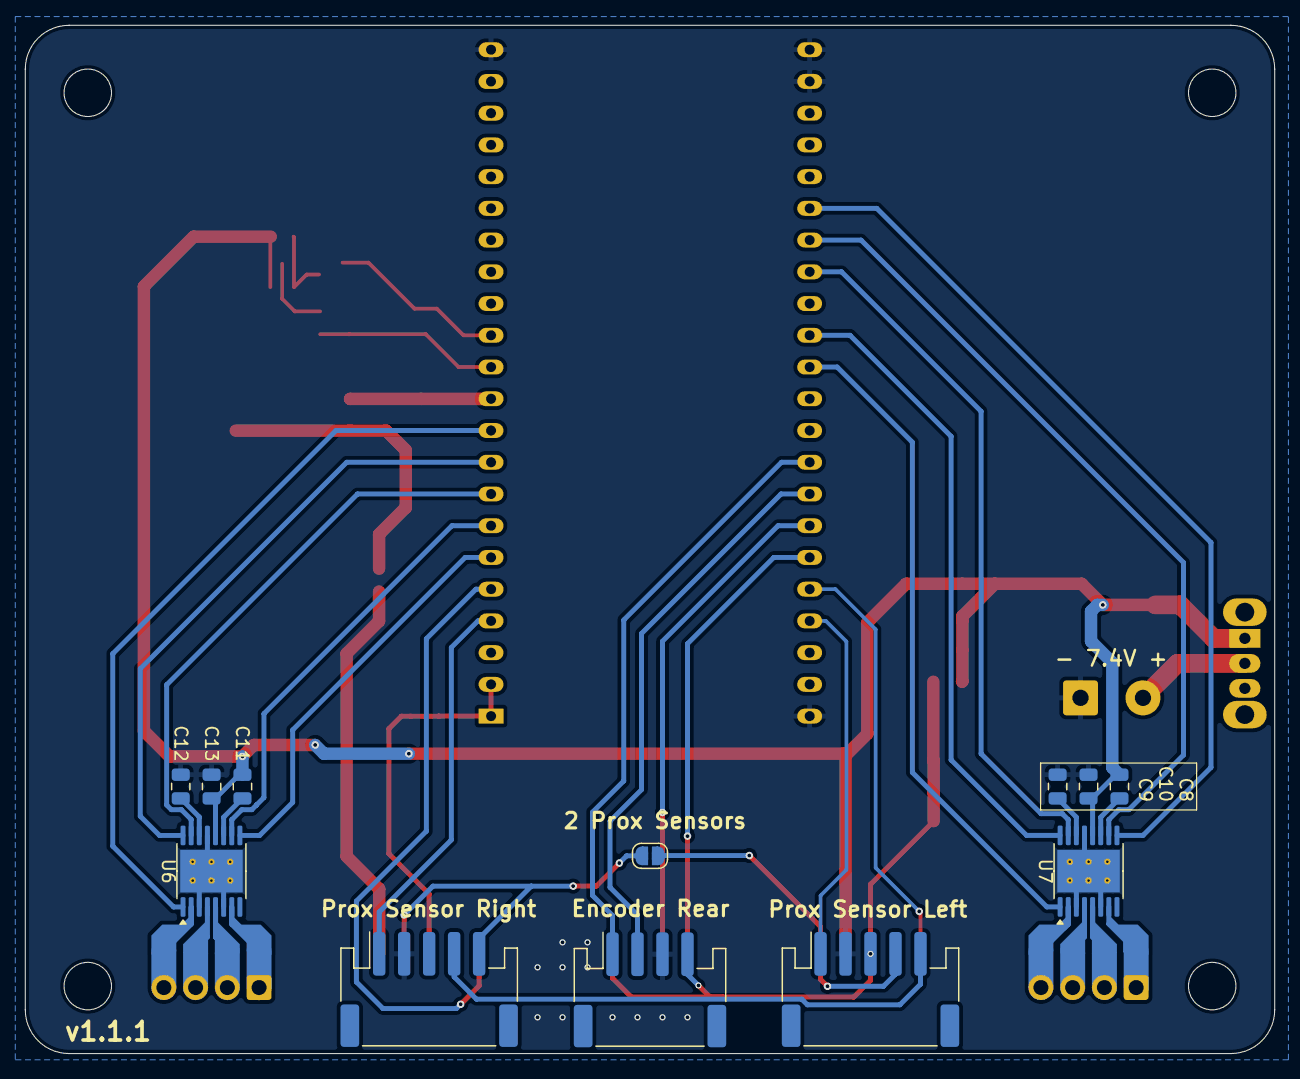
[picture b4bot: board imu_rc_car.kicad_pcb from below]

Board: 2 copper layers, 100.0 x 82.3 mm, 36 parts (13 on the bottom side), 44 nets.
